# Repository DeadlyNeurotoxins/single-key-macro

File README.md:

# single-key-macro
All of the files and documentation required to build and program your own single-key macro using the Digispark Dev Board and Arduino IDE

More info to add later.

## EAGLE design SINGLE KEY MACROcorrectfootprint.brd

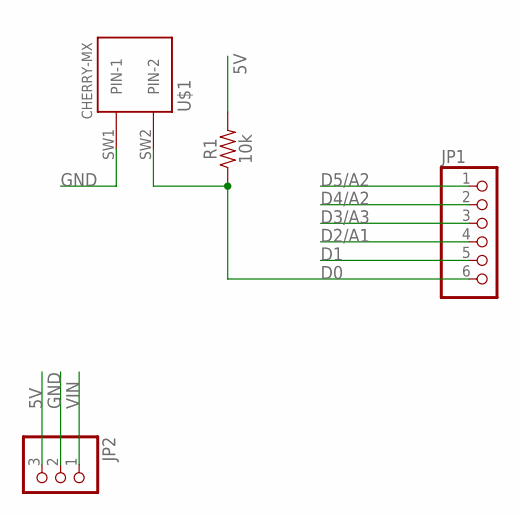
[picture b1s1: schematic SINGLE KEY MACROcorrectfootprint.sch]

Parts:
JP1: PINHD-1X6; 1X06
JP2: PINHD-1X3; 1X03
R1: 10k; AXIAL-0.3
U$1: CHERRY-MX

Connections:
5V: JP2.3, R1.P$2 (2)
D0: JP1.6, R1.P$1 (1), U$1.SW2 (PIN-2)
D1: JP1.5
D2/A1: JP1.4
D3/A3: JP1.3
D4/A2: JP1.2
D5/A2: JP1.1
GND: JP2.2, U$1.SW1 (PIN-1)
VIN: JP2.1

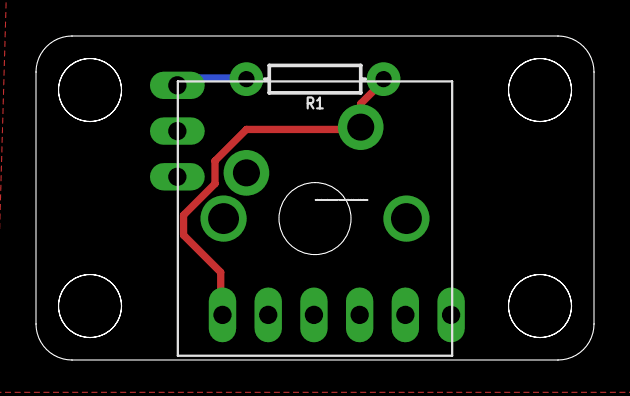
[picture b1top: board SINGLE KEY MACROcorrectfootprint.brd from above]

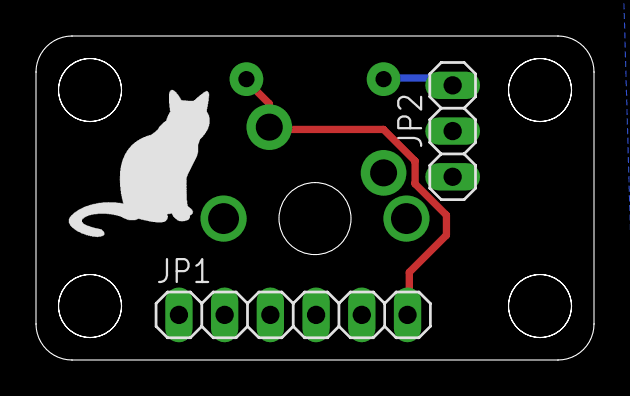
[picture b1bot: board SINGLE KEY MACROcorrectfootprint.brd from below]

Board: 2 copper layers, 31.0 x 18.0 mm, 4 parts (2 on the bottom side), 3 nets.

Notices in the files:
parts and their libraries:
SparkFun-Resistors: Licensing: Creative Commons ShareAlike 4.0 International - https://creativecommons.org/licenses/by-sa/4.0
